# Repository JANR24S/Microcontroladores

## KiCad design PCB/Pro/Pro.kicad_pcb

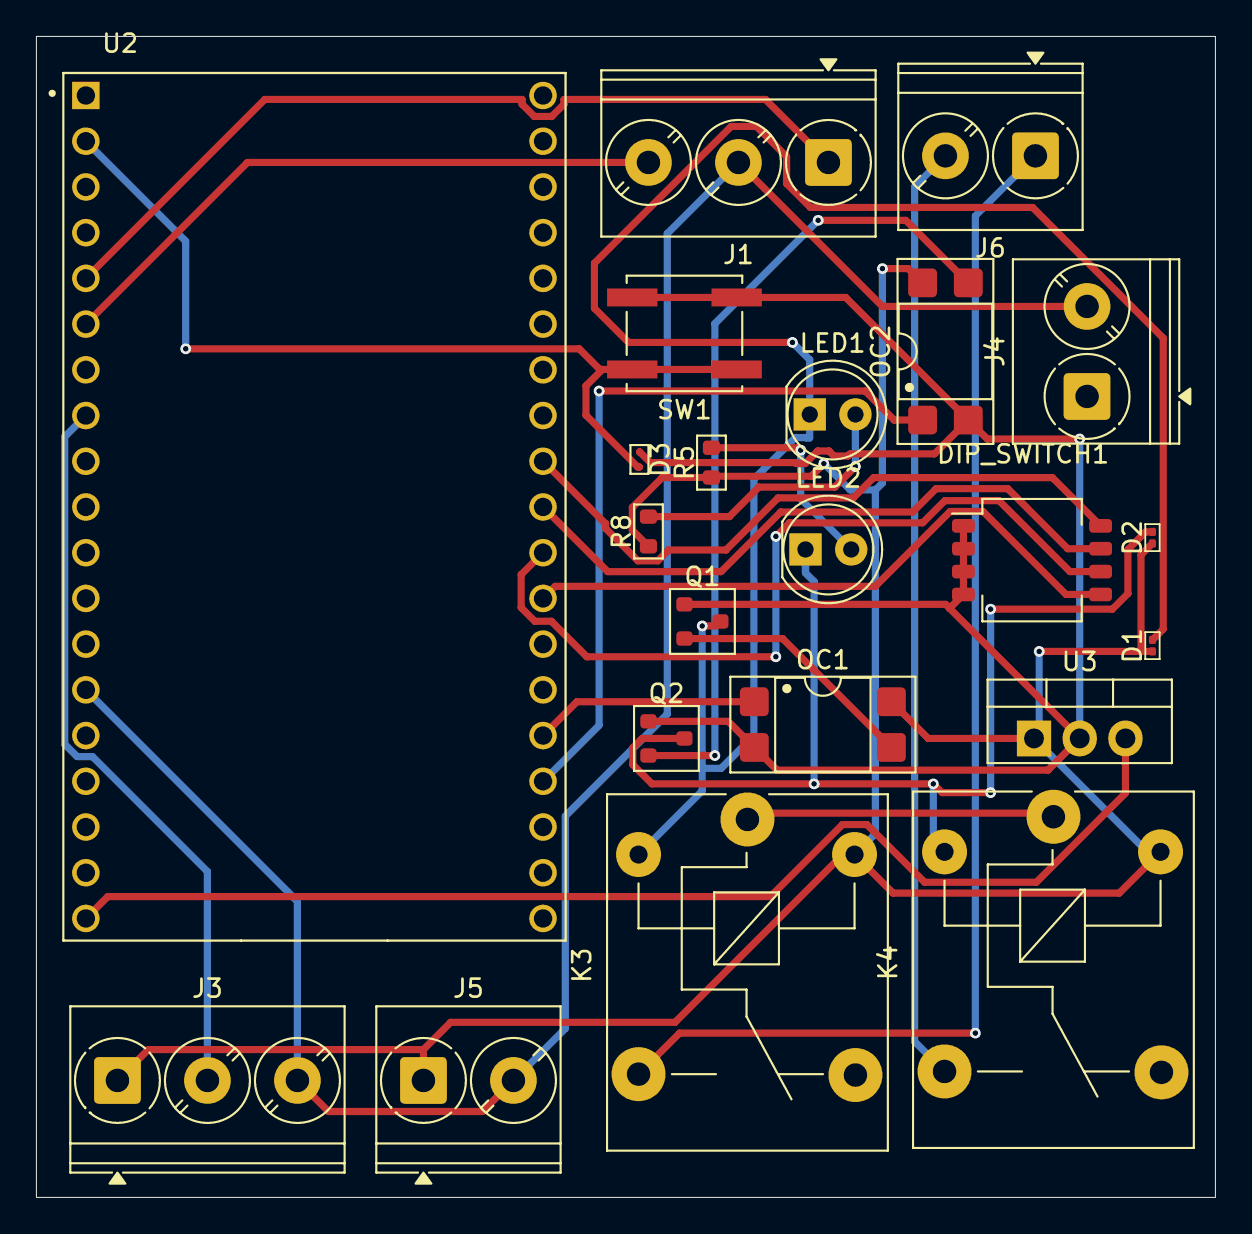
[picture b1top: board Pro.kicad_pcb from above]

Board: 2 copper layers, 65.5 x 64.5 mm, 22 parts (0 on the bottom side), 23 nets.

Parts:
D1, D2: 1N914BWS; D_0201_0603Metric_TVS
D3: ESD9B3.3; D_SOD-923_TVS
DIP_SWITCH1: SW_DIP_x04; SW_DIP_SPSTx04_Slide_KingTek_DSHP04TS_W7.62mm_P1.27mm
J1, J3: Screw_Terminal_01x03; TerminalBlock_Phoenix_PT-1,5-3-5.0-H_1x03_P5.00mm_Horizontal
J4, J5, J6: Screw_Terminal_01x02; TerminalBlock_Phoenix_PT-1,5-2-5.0-H_1x02_P5.00mm_Horizontal
K3, K4: SANYOU_SRD_Form_C; Relay_SPDT_SANYOU_SRD_Series_Form_C
LED1, LED2: LED_0603_Red; LED_D5.0mm
OC1, OC2: PC817; DIP-4_W7.62mm_SMDSocket_SmallPads
Q1, Q2: 2N2219; SOT-23
R5, R8: 2k; R_0603_1608Metric
SW1: SW_Push; SW_Push_1P1T_NO_CK_KSC7xxJ
U2: ESP32-DEVKITC-32U; MODULE_ESP32-DEVKITC-32U
U3: LM7805CT; TO-220-3_Vertical

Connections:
/Micro_Board/12V: D1.1 (K), D2.1 (K), J3.1, J5.1, K3.5, K4.5, OC1.4, OC2.4, R5.1, R8.1, U3.1 (IN)
/Micro_Board/CON_IN_F: J3.2, U2.8 (IO33)
/Micro_Board/L/5V: U2.19 (EXT_5V), U3.3 (OUT)
/Micro_Board/LSA: J1.1, U2.5 (IO34)
/Micro_Board/MICRO/MOTOR A: OC1.1, U2.24 (IO2)
/Micro_Board/MICRO/MOTOR B: OC2.1, U2.23 (IO15)
/Micro_Board/MOTOR 1: J6.1, K3.3
/Micro_Board/MOTOR 2: J6.2, K4.3
/Micro_Board/RST: D3.2 (A), SW1.2, U2.2 (EN)
/Micro_Board/SW1: DIP_SWITCH1.8, U2.30 (IO18)
/Micro_Board/SW2: DIP_SWITCH1.7, U2.29 (IO5)
/Micro_Board/SW3: DIP_SWITCH1.6, U2.28 (IO17)
/Micro_Board/SW4: DIP_SWITCH1.5, U2.27 (IO16)
/Micro_Board/lSC: J1.3, U2.6 (IO35)
Earth: J1.2, J3.3, J4.2, J5.2, U2.14 (GND1)
GND: D3.1 (K), DIP_SWITCH1.1, DIP_SWITCH1.2, DIP_SWITCH1.3, DIP_SWITCH1.4, OC1.2, OC2.2, Q1.1 (E), Q2.1 (E), SW1.1, U3.2
LINE: K3.1, K4.1
unnamed: D1.2 (A), K3.2, LED1.1 (K), Q1.3 (C)
unnamed: D2.2 (A), K4.2, LED2.1 (K), Q2.3 (C)
unnamed: LED1.2 (A), R8.2
unnamed: LED2.2 (A), R5.2
unnamed: OC1.3, Q1.2 (B)
unnamed: OC2.3, Q2.2 (B)

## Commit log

2025-04-24 Create Proyecto FInal
